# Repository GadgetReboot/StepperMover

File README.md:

# StepperMover
Simple 555 and 4011 based A4988 Stepper Controller for quick bench testing of motors

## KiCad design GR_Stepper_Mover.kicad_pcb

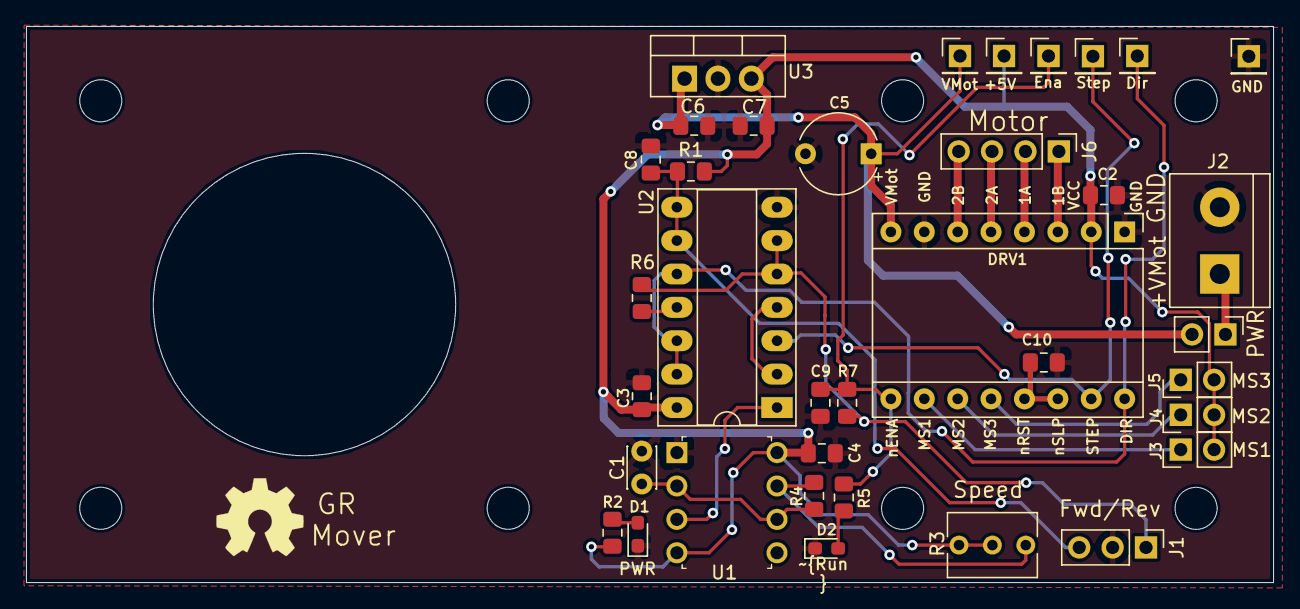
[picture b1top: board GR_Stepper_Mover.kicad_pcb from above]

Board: 2 copper layers, 94.9 x 42.3 mm, 36 parts (0 on the bottom side), 24 nets.

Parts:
C1: 100nF; C_Disc_D3.0mm_W2.0mm_P2.50mm
C2, C3, C4, C6, C7, C9, C10: 100nF; C_0805_2012Metric_Pad1.15x1.40mm_HandSolder
C5: 47uF 50V; CP_Radial_Tantal_D6.0mm_P5.00mm
C8: 470nF; C_0805_2012Metric_Pad1.15x1.40mm_HandSolder
D1, D2: LED; LED_0603_1608Metric_Pad1.05x0.95mm_HandSolder
DRV1: A4988 Module; Pololu_Breakout-16_15.2x20.3mm
J1: Conn_01x03; PinHeader_1x03_P2.54mm_Vertical
J2: Screw_Terminal_01x02; TerminalBlock_bornier-2_P5.08mm
J3, J4, J5: Conn_01x02; PinHeader_1x02_P2.54mm_Vertical
J6: Conn_01x04; PinHeader_1x04_P2.54mm_Vertical
R1: 47K; R_0805_2012Metric_Pad1.15x1.40mm_HandSolder
R2, R5, R7: 1K; R_0805_2012Metric_Pad1.15x1.40mm_HandSolder
R3: 100K; Potentiometer_Vishay_T73XW_Horizontal
R4, R6: 10K; R_0805_2012Metric_Pad1.15x1.40mm_HandSolder
SW1: SW_SPST; PinHeader_1x02_P2.54mm_Vertical
TP1, TP2, TP3, TP4, TP5, TP6: Conn_01x01; PinHeader_1x01_P2.54mm_Vertical
U1: 555; DIP-8_W7.62mm
U2: 4011; DIP-14_W7.62mm_Socket_LongPads
U3: LM7805_TO220; TO-220-3_Vertical

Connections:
/M1_1A: DRV1.4, J6.2
/M1_1B: DRV1.3, J6.1
/M1_2A: DRV1.5, J6.3
/M1_2B: DRV1.6, J6.4
/M1_DIR: DRV1.16, TP5.1, U2.10, U2.12, U2.13
/M1_STEP: DRV1.15, TP4.1, U2.3
/M1_nENA: C9.2, DRV1.9, R5.1, R7.1, TP3.1
GNDREF: C1.2, C2.2, C3.2, C4.2, C5.2, C6.2, C7.2, C8.2, C9.1, C10.2, D1.1, D2.1, DRV1.1, DRV1.7, J1.2, J2.2, TP6.1, U1.1, U2.7, U3.2
unnamed: C1.1, R4.1, U1.2, U1.6
unnamed: C8.1, J1.3, R1.1, U2.8, U2.9
unnamed: C10.1, DRV1.13, DRV1.14
unnamed: D1.2, R2.2
unnamed: D2.2, R5.2
unnamed: DRV1.10, J3.1
unnamed: DRV1.11, J4.1
unnamed: DRV1.12, J5.1
unnamed: J1.1, R6.1, R7.2, U2.5, U2.6
unnamed: J2.1, SW1.1
unnamed: R3.3, R4.2, U1.7
unnamed: R6.2, U2.11
unnamed: U1.3, U2.1
unnamed: U2.2, U2.4
VCC: C2.1, C3.1, C4.1, C7.1, DRV1.2, J3.2, J4.2, J5.2, R1.2, R2.1, R3.1, R3.2, TP2.1, U1.4, U1.8, U2.14, U3.3
Vdrive: C5.1, C6.1, DRV1.8, SW1.2, TP1.1, U3.1
